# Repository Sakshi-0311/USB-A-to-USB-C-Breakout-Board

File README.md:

# USB-A-to-USB-C-Breakout-Board

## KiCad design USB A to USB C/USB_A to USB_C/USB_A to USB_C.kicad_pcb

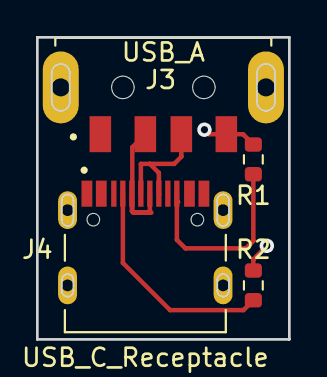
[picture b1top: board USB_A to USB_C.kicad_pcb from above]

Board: 2 copper layers, 14.0 x 16.8 mm, 4 parts (0 on the bottom side), 5 nets.

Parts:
J3: USB_A; MOLEX_480-37-1000
J4: USB_C_Receptacle; HRO_TYPE-C-31-M-12
R1, R2: 5.1k; R_0603_1608Metric

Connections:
GND: J3.4, R1.2, R2.2
unnamed: J3.2, J4.A7, J4.B7
unnamed: J3.3, J4.A6, J4.B6
unnamed: J4.A5, R2.1
unnamed: J4.B5, R1.1

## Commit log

2021-06-03 Added Schematics, Routing and 3D models
2021-06-03 Added Component Libraries and 3D models
2021-06-03 Added Screenshots of Schematics and 3D view
